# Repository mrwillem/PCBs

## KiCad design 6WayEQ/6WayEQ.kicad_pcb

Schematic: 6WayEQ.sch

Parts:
C1: C
C7, C13, C14, C18, C19, C20, C54, C58, C66: 100 nF; R_0805_HandSolder
C11, C12: 470 uF; CP_Radial_D10.0mm_P2.50mm_P5.00mm
C21, C22, C23: 10 uF; CP_Radial_D5.0mm_P2.00mm
C24, C40: 68nF; Capacitor-Wima-SMD2824-63v-L7,2
C25: 15nF; C_1210_HandSoldering
C26: 68p
C27: 47n; C_1812_HandSoldering
C28, C32, C41, C42, C43, C44, C53, C57: 100nF; R_0805_HandSolder
C29: 10n; C_1206_HandSoldering
C30, C33, C48: 33nF; C_1210_HandSoldering
C31, C35, C62, C63: 100n; R_0805_HandSolder
C34: 6.8nF; C_1206_HandSoldering
C36: 100nF; C_1812_HandSoldering
C37: 1uF; Capacitor-Wima-SMD2824-63v-L7,2
C38, C39: 220nF; C_1812_HandSoldering
C45: 470nF; Capacitor-Wima-SMD2824-63v-L7,2
C46, C47: 150nF; C_1812_HandSoldering
C49: 47nF; C_1812_HandSoldering
C50: 68 pF
C51: 1 uF; Capacitor-Wima-SMD2824-63v-L7,2
C52: 47p
C55, C56: 22pF
C59, C64: 10uF; C_Rect_L26.5mm_W8.5mm_P22.50mm_MKS4
C60: 220nF; Capacitor-Wima-SMD2824-63v-L7,2
C61: 10nF; C_1206_HandSoldering
C65: 10 uF; C_Rect_L26.5mm_W8.5mm_P22.50mm_MKS4
D1, D3: DIODE; D_SMB_Handsoldering
D2, D15: D_TVS
D4, D12: D_Schottky_x2_Serial_AKC
D5, D6, D7, D8: BY500; D_SMB_Handsoldering
D9, D10, D11: DIODE
D13, D14, D17, D18: DIODE; D_DO-41_SOD81_P7.62mm_Horizontal
D16: LED
J1, J2, J3, J4: CONN_01X01; MountingHole_4.3mm_M4
K2, K3: CONN_3; Molex_MicroLatch-53253-0370_03x2.00mm_Straight
K4: EQLEVEL; Molex_MicroLatch-53253-0370_03x2.00mm_Straight
K10: TONE 25K; Molex_MicroLatch-53253-0370_03x2.00mm_Straight
K11: LEVEL 100K; Molex_MicroLatch-53253-0370_03x2.00mm_Straight
P1, P15, P16, P17, P19, P20, P21: TONE 25K; Molex_MicroLatch-53253-0370_03x2.00mm_Straight
P2, P4, P9, P10, P12, P13, P14: CONN_2; Molex_MicroLatch-53253-0370_03x2.00mm_Straight
P3: CHASSISGROUND
P11: DRIVEPOT; Molex_MicroLatch-53253-0370_03x2.00mm_Straight
P18: CONN_4; Molex_MicroLatch-53253-0370_03x2.00mm_Straight
P22: VOICE_10K; Molex_MicroLatch-53253-0370_03x2.00mm_Straight
R1, R55: R; R_0805_HandSolder
R2: 10R 5W
R3, R4: 10R
R5, R26, R27: 20K; R_0805_HandSolder
R6, R34: 1M; R_0805_HandSolder
R7, R13, R21, R23, R24: 470r; R_0805_HandSolder
R8: 1K
R9, R22, R49: 470R; R_0805_HandSolder
R10, R31, R37, R39, R41: 1K; R_0805_HandSolder
R11: 100K
R14, R19: 24K; R_0805_HandSolder
R15, R48: 0-1K; R_0805_HandSolder
R18, R46: 4K7; R_0805_HandSolder
R20: 22K; R_0805_HandSolder
R25: 390r; R_0805_HandSolder
R30: 47K; R_0805_HandSolder
R38: 220R; R_0805_HandSolder
R40, R47: 10K; R_0805_HandSolder
R42: 2K2; R_0805_HandSolder
R43: 100K; R_0805_HandSolder
R44, R45: 2K4; R_0805_HandSolder
U1: ADG5413F; TSSOP-16_4.4x5mm_Pitch0.65mm
U3: LM7809ACT; TO-252-2_Rectifier
U4: LM7815ACT; TO-252-2_Rectifier
U5: LM7915CT; TO-252-2_Rectifier
U6, U7, U11, U12, U14, U22: OPA1642; SO-8_5.3x6.2mm_Pitch1.27mm
U13: JRC4558D; DIP-8_W7.62mm_Socket
U21: LDRSWITCH; Optoisolator_NSL-32

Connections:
9V: C65.1, C66.1, D4.2, D12.2, P18.4
100HZ: C37.1, P1.1
200HZ: C45.1, P20.1
400HZ: C39.1, P19.1
800HZ: C47.1, P21.1
1600HZ: C24.1, P16.1
3200HZ: C33.1, P17.1
6400HZ: C30.1, P15.1
AGND: C26.1, C29.2, C49.2, C61.1, K4.1, P10.2 (PM), P12.2 (PM), R5.2, R6.2, R10.2, R14.2, R19.2, R20.2, R26.2, R27.2, R47.2, R55.1
Direct_Wah_Out: P2.1, U1.2, U1.16
EQCIRCUITIN: C26.2, C27.1, P12.1
EQCIRCUITOUT: C64.2, P10.1, R47.1
GND: C7.1, C11.2, C12.1, C13.2, C14.1, C18.2, C19.2, C20.1, C21.2, C22.2, C23.1, C28.2, C31.1, C32.1, C35.2, C41.2, C42.2, C43.1, C44.1, C53.2, C54.1, C57.1, C58.2, C62.1, C63.2, D5.1 (A), D7.2 (K), D9.1 (A), D10.2 (K), D11.1 (A), K2.2 (PM), P9.2 (PM), R2.1, R55.2, U3.2 (GND), U4.2 (GND), U5.1 (GND)
NegativeEQ: C36.2, P1.2 (PM), P15.2 (PM), P16.2 (PM), P17.2 (PM), P19.2 (PM), P20.2 (PM), P21.2 (PM), R45.2, U22.2 (IN-_1)
unnamed: C7.2, D6.1 (A), D8.2 (K), P3.1, R2.2
unnamed: C11.1, D1.2 (K), U4.1 (IN)
unnamed: C12.2, C14.2, D3.1 (A), U5.2 (IN)
unnamed: C13.1, U3.1 (IN)
unnamed: C18.1, C21.1, D9.2 (K), P9.1, U3.3 (OUT)
unnamed: C22.1, D11.2 (K), U4.3 (OUT)
unnamed: C23.2, D10.1 (A), U5.3 (OUT)
unnamed: C24.2, C25.1, R7.1
unnamed: C25.2, R5.1, U6.3 (IN+_1)
unnamed: C27.2, R6.1, R9.1
unnamed: C29.1, R22.1
unnamed: C30.2, R10.1
unnamed: C33.2, C34.1, R13.1
unnamed: C34.2, R14.1, U6.5 (IN+_2)
unnamed: C36.1, R45.1, R46.2, U22.1 (OUT_1)
unnamed: C37.2, C38.1, R21.1
unnamed: C38.2, R19.1, U11.3 (IN+_1)
unnamed: C39.2, C40.1, R23.1
unnamed: C40.2, R20.1, U12.3 (IN+_1)
unnamed: C45.2, C46.1, R24.1
unnamed: C46.2, R26.1, U11.5 (IN+_2)
unnamed: C47.2, C48.1, R25.1
unnamed: C48.2, R27.1, U12.5 (IN+_2)
unnamed: C49.1, P22.1
unnamed: C51.2, R34.1, U14.3 (IN+_1)
unnamed: C52.1, D17.1 (A), D18.2 (K), P11.1, R37.1, U13.1 (OUT_1)
unnamed: C52.2, D13.2 (K), D14.1 (A), R30.2, R31.1, U13.2 (IN-_1)
unnamed: C55.2, K10.3, R37.2, U13.5 (IN+_2)
unnamed: C56.1, K10.2 (PM)
unnamed: C56.2, R38.2
unnamed: C59.1, U14.6 (IN-_2), U14.7 (OUT_2)
unnamed: C60.1, D4.3, R42.1
unnamed: C61.2, R46.1, U22.5 (IN+_2)
unnamed: C64.1, R49.2
unnamed: D1.1 (A), D3.2 (K), K2.3
unnamed: D5.2 (K), D6.2 (K), D7.1 (A), D8.1 (A)
unnamed: D13.1 (A), D17.2 (K)
unnamed: D14.2 (K), D18.1 (A)
unnamed: K3.1, R43.1
unnamed: K3.2 (PM), R43.2, U21.3 (Audio1)
unnamed: K3.3, U21.2 (AUDIO)
unnamed: K4.2 (PM), R15.1
unnamed: K4.3, U7.1 (OUT_1), U7.2 (IN-_1)
unnamed: K10.1, R39.2, U13.6 (IN-_2)
unnamed: K11.1, R41.1
unnamed: K11.2 (PM), U14.5 (IN+_2)
unnamed: P11.2 (PM), R30.1
unnamed: P22.2 (PM), R31.2
unnamed: R7.2, U6.1 (OUT_1), U6.2 (IN-_1)
unnamed: R9.2, U7.3 (IN+_1)
unnamed: R13.2, U6.6 (IN-_2), U6.7 (OUT_2)
unnamed: R15.2, U7.5 (IN+_2)
unnamed: R18.1, R22.2, U7.6 (IN-_2)
unnamed: R18.2, R44.1, U7.7 (OUT_2)
unnamed: R21.2, U11.1 (OUT_1), U11.2 (IN-_1)
unnamed: R23.2, U12.1 (OUT_1), U12.2 (IN-_1)
unnamed: R24.2, U11.6 (IN-_2), U11.7 (OUT_2)
unnamed: R25.2, U12.6 (IN-_2), U12.7 (OUT_2)
unnamed: R39.1, R41.2, U13.7 (OUT_2)
unnamed: R42.2, U21.4 (LEDGND)
unnamed: R48.1, U13.3 (IN+_1)
unnamed: R48.2, U14.1 (OUT_1), U14.2 (IN-_1)
unnamed: R49.1, U22.6 (IN-_2), U22.7 (OUT_2)
unnamed: U1.9, U1.15
PositiveEQ: P1.3, P15.3, P16.3, P17.3, P19.3, P20.3, P21.3, R44.2, U22.3 (IN+_1)
TSCIRCUITIN: C50.1, C51.1, P14.2 (PM)
TSCIRCUITOUT: C59.2, P13.2 (PM), R40.2
VDD: C32.2, C35.1, C43.2, C44.2, C57.2, C58.1, C63.1, U1.13, U6.8 (VDD), U7.8 (VDD), U11.8 (VDD), U12.8 (VDD), U13.8 (VDD), U14.8 (VDD), U22.8 (VDD)
VSS: C28.1, C31.2, C41.1, C42.1, C53.1, C54.2, C62.2, U1.4, U6.4 (VSS), U7.4 (VSS), U11.4 (VSS), U12.4 (VSS), U13.4 (VSS), U14.4 (VSS), U22.4 (VSS)
WAHFOOT: D12.3, U1.3, U1.11, U1.14
WAHGND: C60.2, C65.2, C66.2, D4.1, D12.1, P2.2 (PM), P4.2 (PM), P18.3, U1.5, U1.6, U1.7, U1.8, U21.1 (LED-)
WAH_IN: P4.1, U1.1, U1.10

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
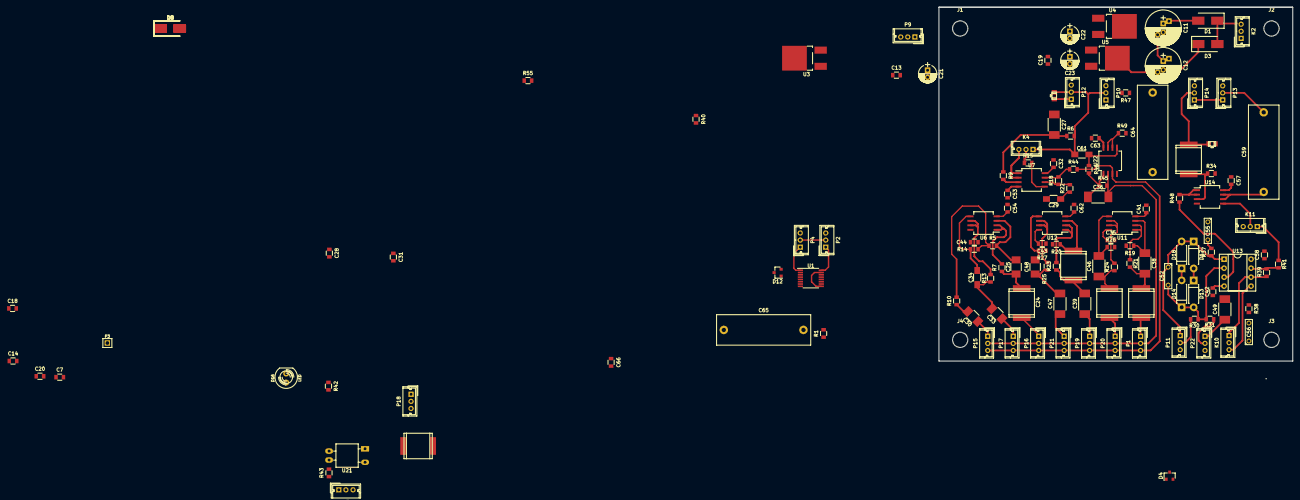
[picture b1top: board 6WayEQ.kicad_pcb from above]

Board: 2 copper layers, 100.0 x 105.0 mm, 142 parts (0 on the bottom side), 87 nets.

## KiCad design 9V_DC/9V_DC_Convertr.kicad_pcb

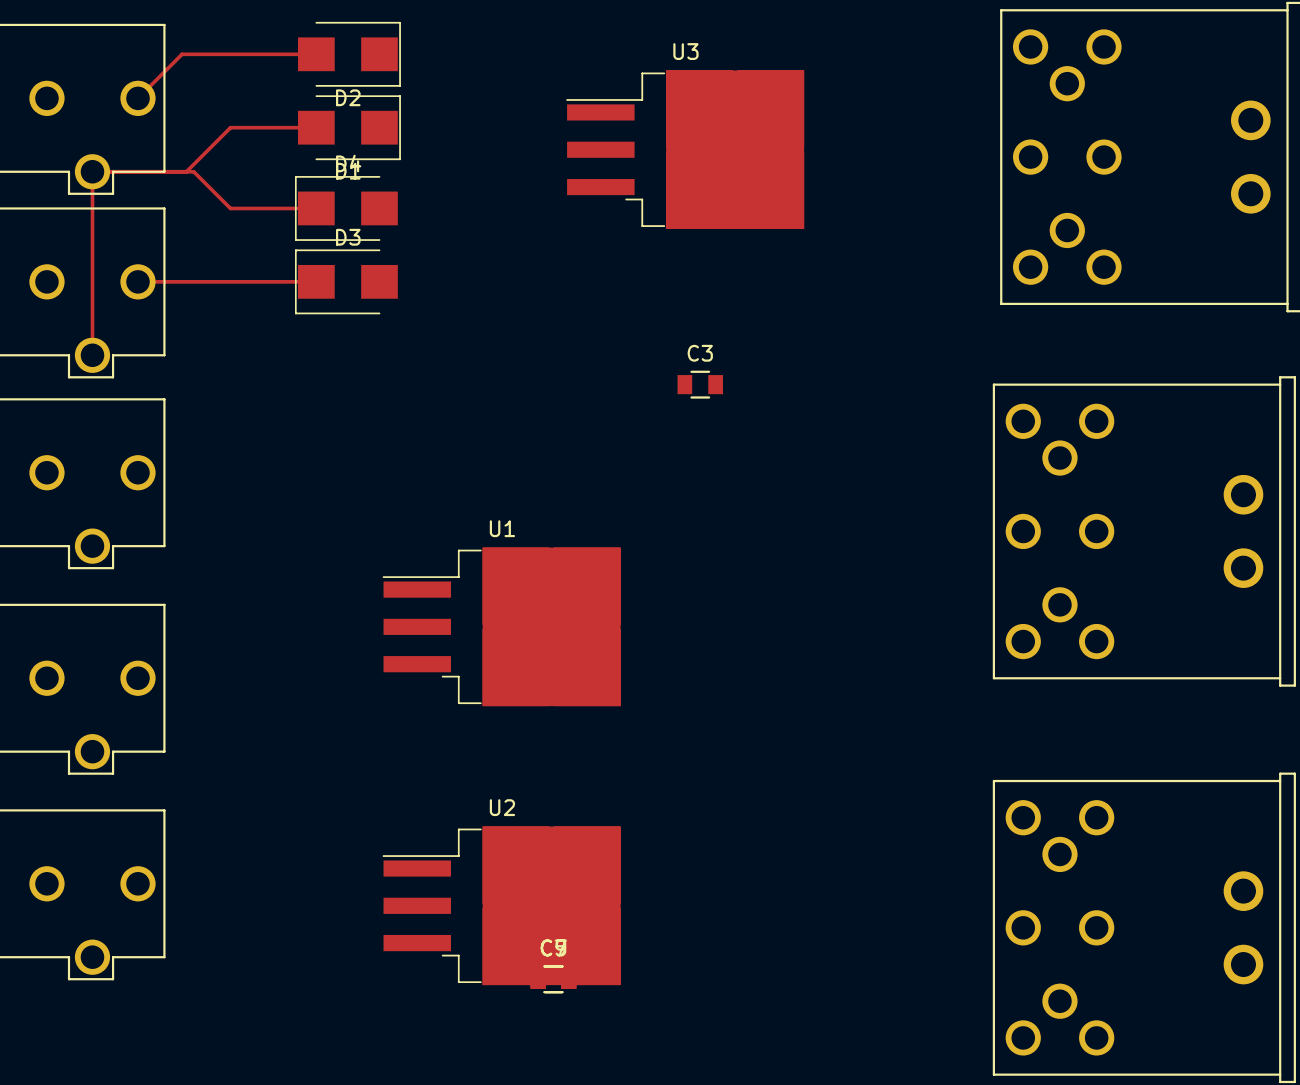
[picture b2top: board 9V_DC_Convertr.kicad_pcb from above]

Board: 2 copper layers, 19 parts (0 on the bottom side), 7 nets.

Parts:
C3, C5, C7, C9: 100 nF; R_0805_HandSolder
D1, D2, D3, D4: D; D_SMB
J1, J2, J3, J6, J7: CONN_01X02; BARREL_JACK_CLIFF_FC681465P
J4: CONN_01X07; CLIFF_DIN7SA
J5: CONN_01X02; CLIFF_DIN7SA
J8: DIN_5; CLIFF_DIN7SA
U1, U2, U3: LM7809ACT; TO-263-3_TabPin2

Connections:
9V_AC: D1.2, D4.1, J1.2, J5.2, J7.2
9V_AC2: D2.2, D3.1, J1.1, J5.1, J7.1
+9V: C3.1, D1.1, D2.1, U1.1, U2.1, U3.1
GND: C3.2, C5.2, C7.2, C9.2, D3.2, D4.2, J2.2, J3.2, J6.2, U1.2, U2.2, U3.2
unnamed: C5.1, J2.1, U1.3
unnamed: C7.1, J3.1, U2.3
unnamed: C9.1, J6.1, U3.3

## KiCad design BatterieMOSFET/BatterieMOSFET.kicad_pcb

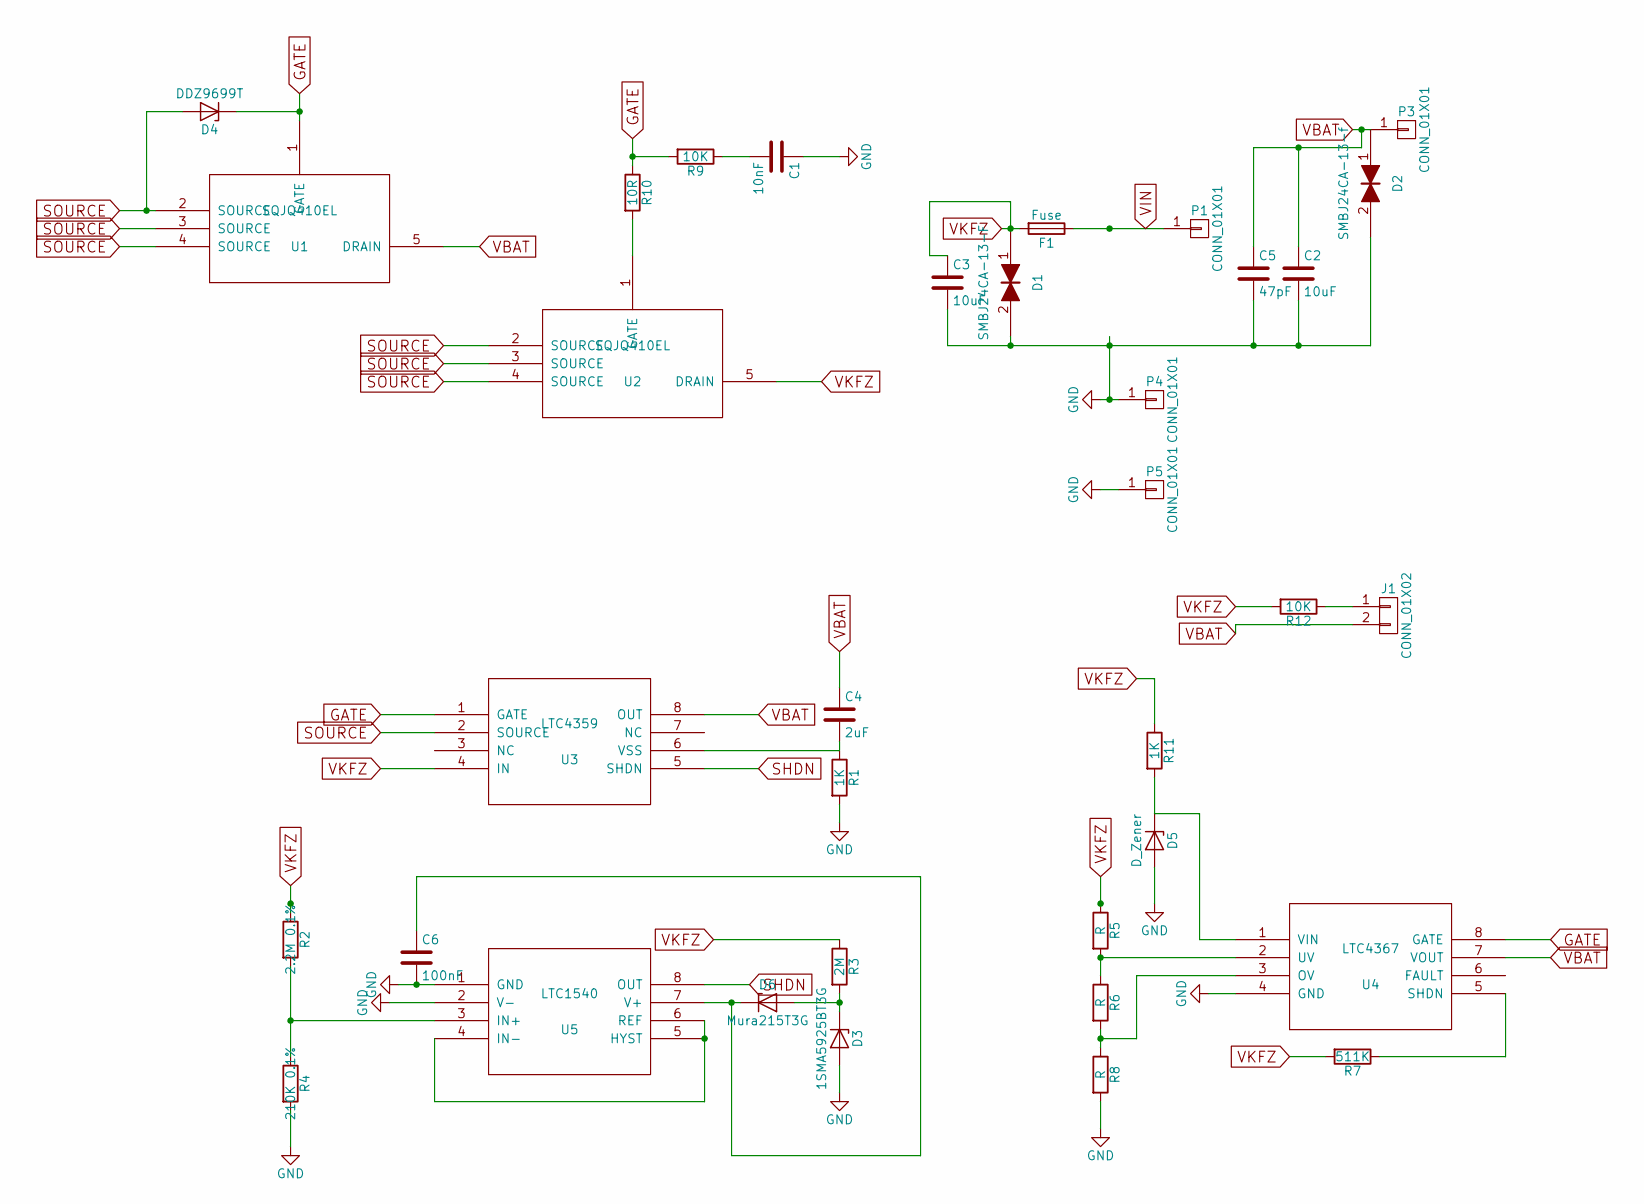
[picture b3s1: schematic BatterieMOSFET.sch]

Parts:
C1: 10nF; C_0805
C2, C3: 10uF; C_1210
C4: 2uF; C_0805
C5: 47pF; C_0805
C6: 100nF; C_0805
D1: SMBJ24CA-13-F; D_SMB
D2: SMBJ24CA-13-f; D_SMB
D3: 1SMA5925BT3G; D_SMA
D4: DDZ9699T; D_SOD-523
D5: D_Zener; D_SMA
D6: Mura215T3G; D_SMA
F1: Fuse; Keystone_3557_2
J1: CONN_01X02; PINHEAD1-2
P1, P3, P4, P5: CONN_01X01; MountingHole_4.3mm_M4_Pad_Via
R1: 1K; R_0603_HandSolder
R2: 2.2M 0.1%; R_0603_HandSolder
R3: 2M; R_0603_HandSolder
R4: 210K 0.1%; R_0603_HandSolder
R5, R6, R8: R; R_0603_HandSolder
R7: 511K; R_0603_HandSolder
R9, R12: 10K; R_0805_HandSolder
R10: 10R; R_0805_HandSolder
R11: 1K; R_0805_HandSolder
U1, U2: SQJQ410EL; PowerPAK_8x8L
U3: LTC4359; MSOP-8_3x3mm_Pitch0.65mm
U4: LTC4367; MSOP-8_3x3mm_Pitch0.65mm
U5: LTC1540; MSOP-8_3x3mm_Pitch0.65mm

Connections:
GATE: D4.1 (K), R9.2, R10.1, U1.1 (GATE), U3.1 (GATE), U4.8 (GATE)
GND: C1.1, C2.2, C3.2, C5.2, C6.2, D1.2, D2.2, D3.2 (A), D5.2 (A), P4.1, P5.1, R1.2, R4.2, R8.2, U4.4 (GND), U5.1 (GND), U5.2 (V-)
unnamed: C1.2, R9.1
unnamed: C4.2, R1.1, U3.6 (VSS)
unnamed: C6.1, D6.1 (K), U5.7 (V+)
unnamed: D3.1 (K), D6.2 (A), R3.2
unnamed: D5.1 (K), R11.2, U4.1 (VIN)
unnamed: J1.1, R12.1
unnamed: R2.2, R4.1, U5.3 (IN+)
unnamed: R5.2, R6.1, U4.2 (UV)
unnamed: R6.2, R8.1, U4.3 (OV)
unnamed: R7.1, U4.5 (SHDN)
unnamed: R10.2, U2.1 (GATE)
unnamed: U5.4 (IN-), U5.5 (HYST), U5.6 (REF)
SHDN: U3.5 (SHDN), U5.8 (OUT)
SOURCE: D4.2 (A), U1.2 (SOURCE), U1.3 (SOURCE), U1.4 (SOURCE), U2.2 (SOURCE), U2.3 (SOURCE), U2.4 (SOURCE), U3.2 (SOURCE)
VBAT: C2.1, C4.1, C5.1, D2.1, J1.2, P3.1, U1.5 (DRAIN), U3.8 (OUT), U4.7 (VOUT)
VIN: F1.1, P1.1
VKFZ: C3.1, D1.1, F1.2, R2.1, R3.1, R5.1, R7.2, R11.1, R12.2, U2.5 (DRAIN), U3.4 (IN)

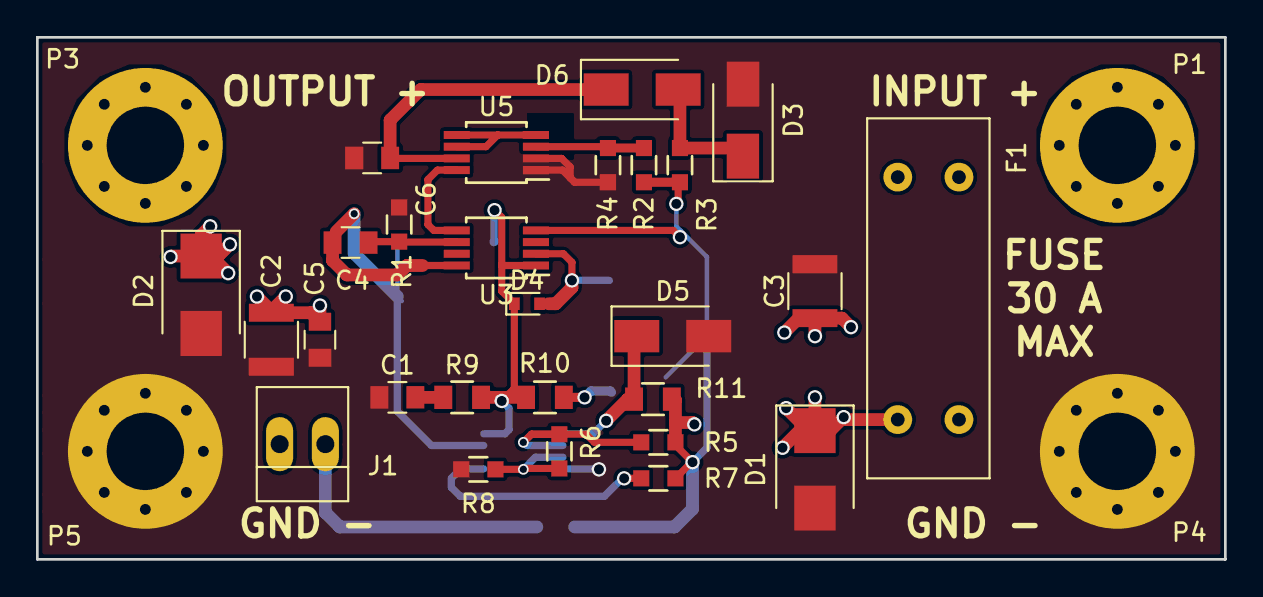
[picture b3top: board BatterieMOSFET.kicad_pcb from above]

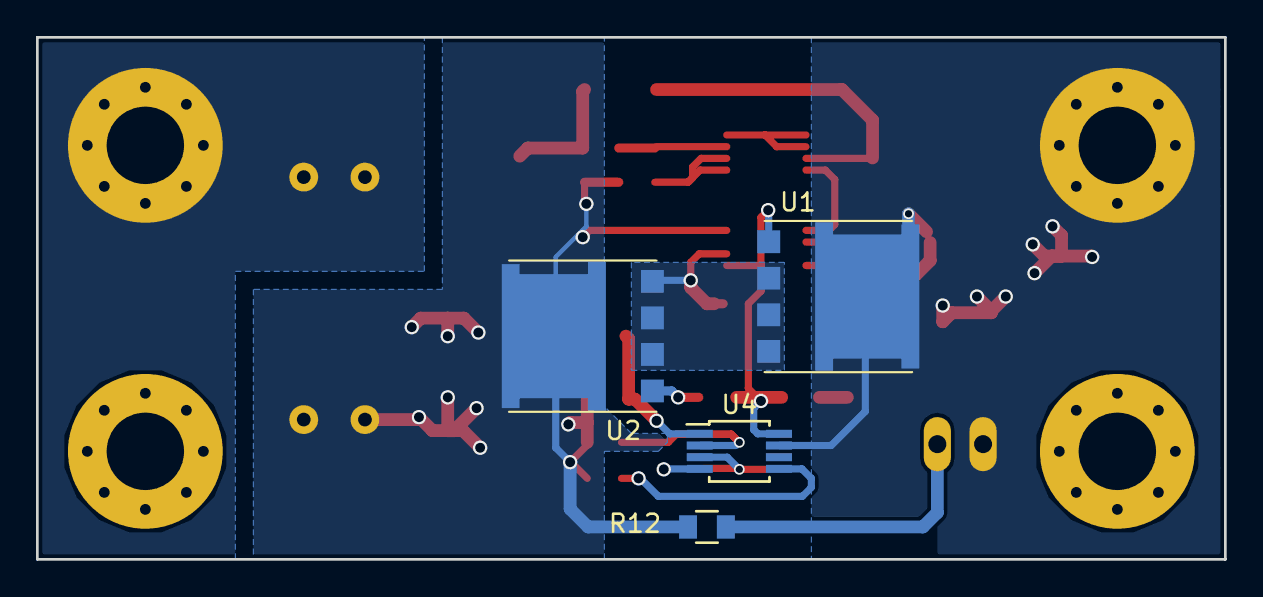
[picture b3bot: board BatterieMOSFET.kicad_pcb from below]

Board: 2 copper layers, 66.0 x 29.0 mm, 35 parts (4 on the bottom side), 19 nets.
